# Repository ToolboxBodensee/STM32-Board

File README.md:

# STM32-Board

**Entwicklung nur auf [GitLab](https://gitlab.com/ToolboxBodensee/microcontroller/STM32-Board). Auf GitHub befindet sich lediglich ein Mirror**

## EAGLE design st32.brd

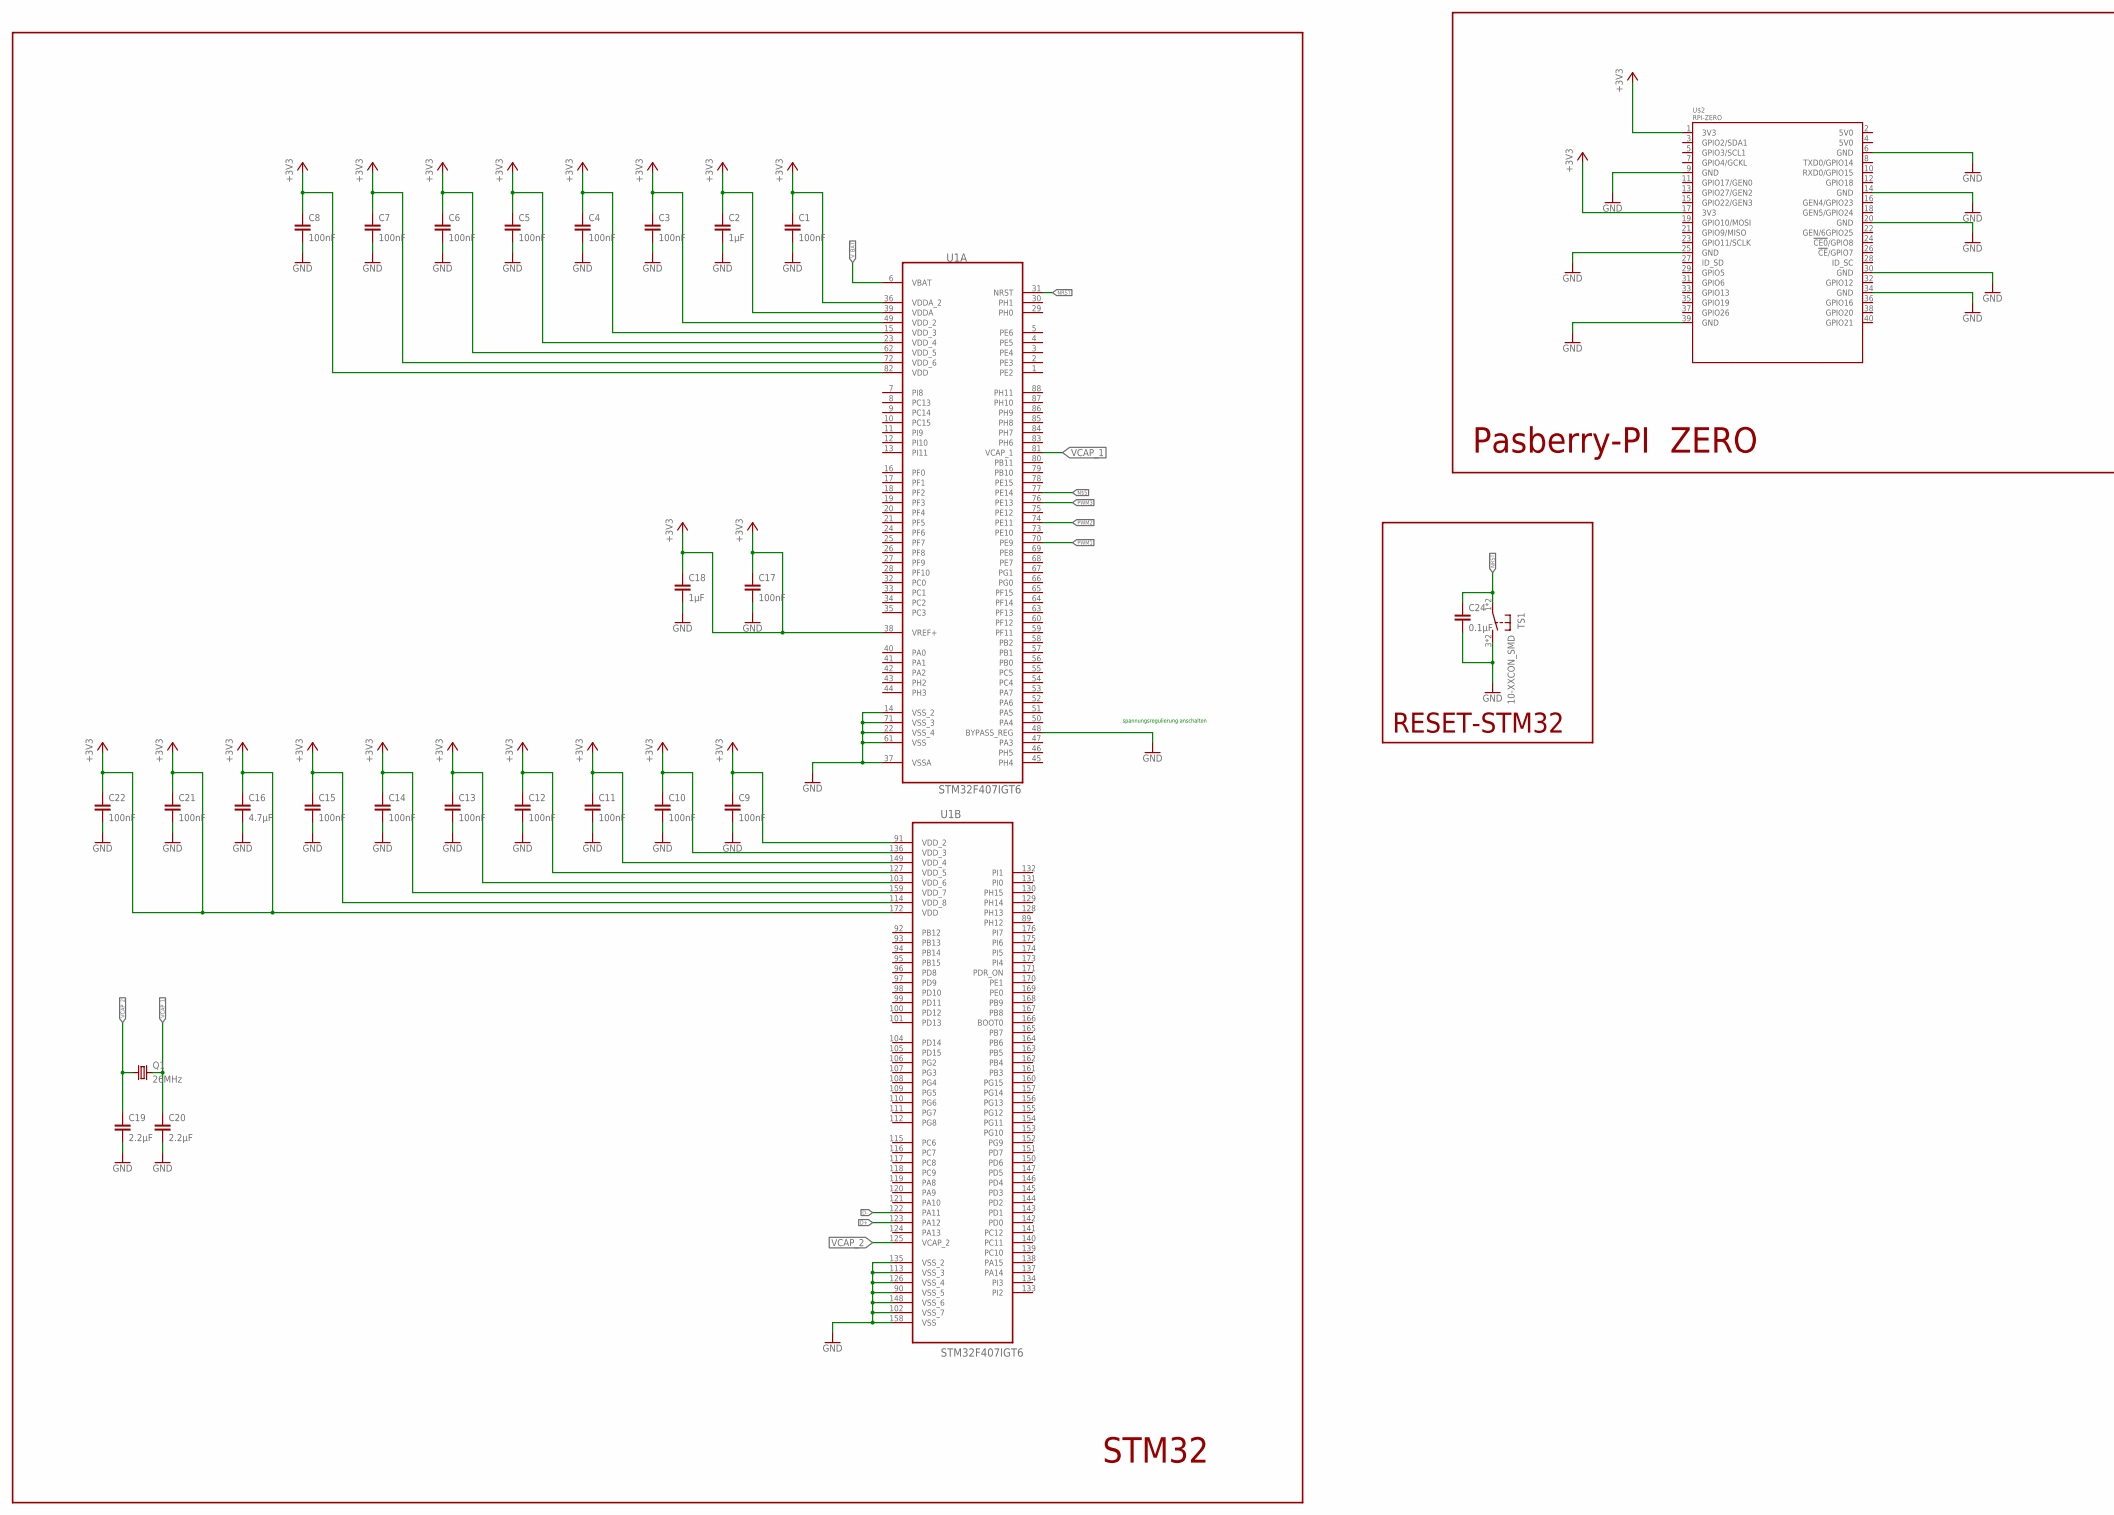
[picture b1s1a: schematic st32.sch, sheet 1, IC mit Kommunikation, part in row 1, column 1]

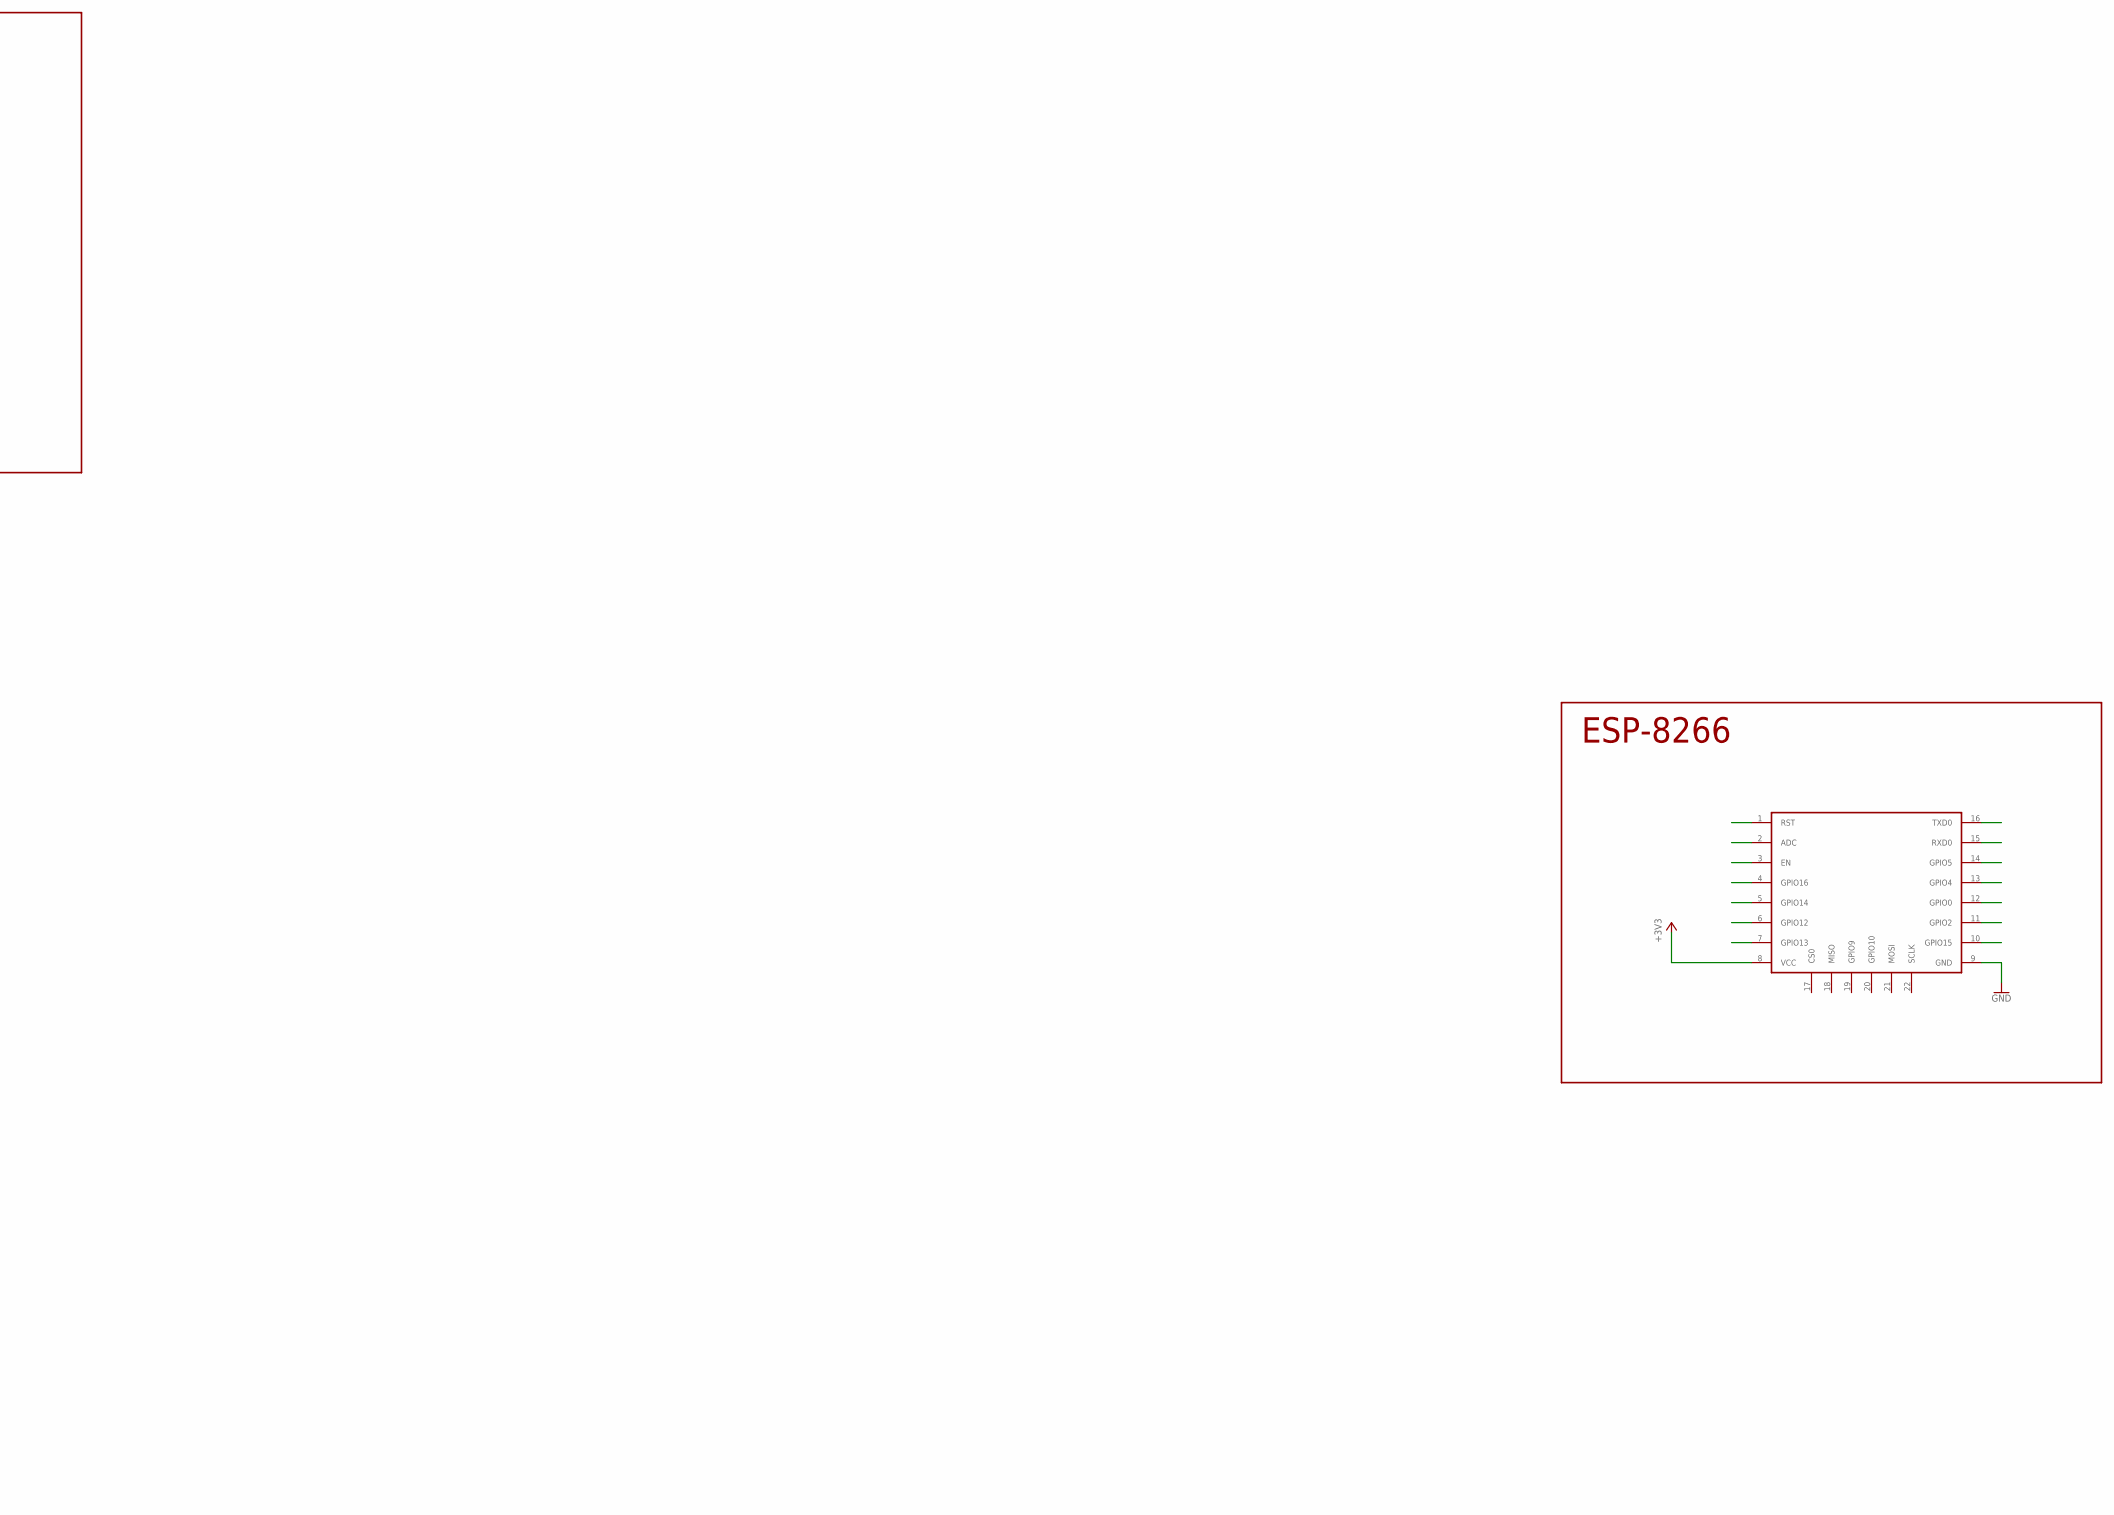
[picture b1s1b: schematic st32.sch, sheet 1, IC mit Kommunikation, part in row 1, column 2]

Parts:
C1, C3, C4, C5, C6, C7, C8, C9, C10, C11, C12, C13, C14, C15, C17, C21, C22: 100nF; C0603
C2, C18: 1µF; C0603
C16: 4.7µF; C0603
C19, C20: 2.2µF; C0603
C24: 0.1µF; C0603
Q1: 26MHz; HC49UP
TS1: 10-XXCON_SMD; SKHMPXE010
U1: STM32F407IGT6; QFP50P2600X2600X160-176N
U$1: ESP8266; ESP8266-SMT
U$2: RPI-ZERO; RASPBERRYPI_BASTELSTUBE_V13_RASPI_BOARD_B+_FULL

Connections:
+3V3: C1.1, C2.1, C3.1, C4.1, C5.1, C6.1, C7.1, C8.1, C9.1, C10.1, C11.1, C12.1, C13.1, C14.1, C15.1, C16.1, C17.1, C18.1, C21.1, C22.1, U1.15 (VDD_3), U1.23 (VDD_4), U1.36 (VDDA_2), U1.38 (VREF+), U1.39 (VDDA), U1.49 (VDD_2), U1.62 (VDD_5), U1.72 (VDD_6), U1.82 (VDD), U1.91 (VDD_2), U1.103 (VDD_6), U1.114 (VDD_8), U1.127 (VDD_5), U1.136 (VDD_3), U1.149 (VDD_4), U1.159 (VDD_7), U1.172 (VDD), U$1.8 (VCC), U$2.1 (3V3), U$2.17 (3V3); also elsewhere on the board
D+: U1.123 (PA12); also elsewhere on the board
D-: U1.122 (PA11); also elsewhere on the board
GND_PWR: C1.2, C2.2, C3.2, C4.2, C5.2, C6.2, C7.2, C8.2, C9.2, C10.2, C11.2, C12.2, C13.2, C14.2, C15.2, C16.2, C17.2, C18.2, C19.2, C20.2, C21.2, C22.2, C24.2, TS1.3 (S), TS1.4 (S), U1.14 (VSS_2), U1.22 (VSS_4), U1.37 (VSSA), U1.48 (BYPASS_REG), U1.61 (VSS), U1.71 (VSS_3), U1.90 (VSS_5), U1.102 (VSS_7), U1.113 (VSS_3), U1.126 (VSS_4), U1.135 (VSS_2), U1.148 (VSS_6), U1.158 (VSS), U$1.9 (GND), U$2.6 (GND), U$2.9 (GND), U$2.14 (GND), U$2.20 (GND), U$2.25 (GND), U$2.30 (GND), U$2.34 (GND), U$2.39 (GND); also elsewhere on the board
NRST: C24.1, TS1.1, TS1.2, U1.31 (NRST)
PWM1: U1.70 (PE9)
PWM2: U1.74 (PE11)
PWM3: U1.76 (PE13)
VCAP_1: C20.1, Q1.2, U1.81 (VCAP_1)
VCAP_2: C19.1, Q1.1, U1.125 (VCAP_2)
V_BAT: U1.6 (VBAT); also elsewhere on the board

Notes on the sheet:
spannungsregulierung anschalten
STM32
Pasberry-PI ZERO
ESP-8266
RESET-STM32

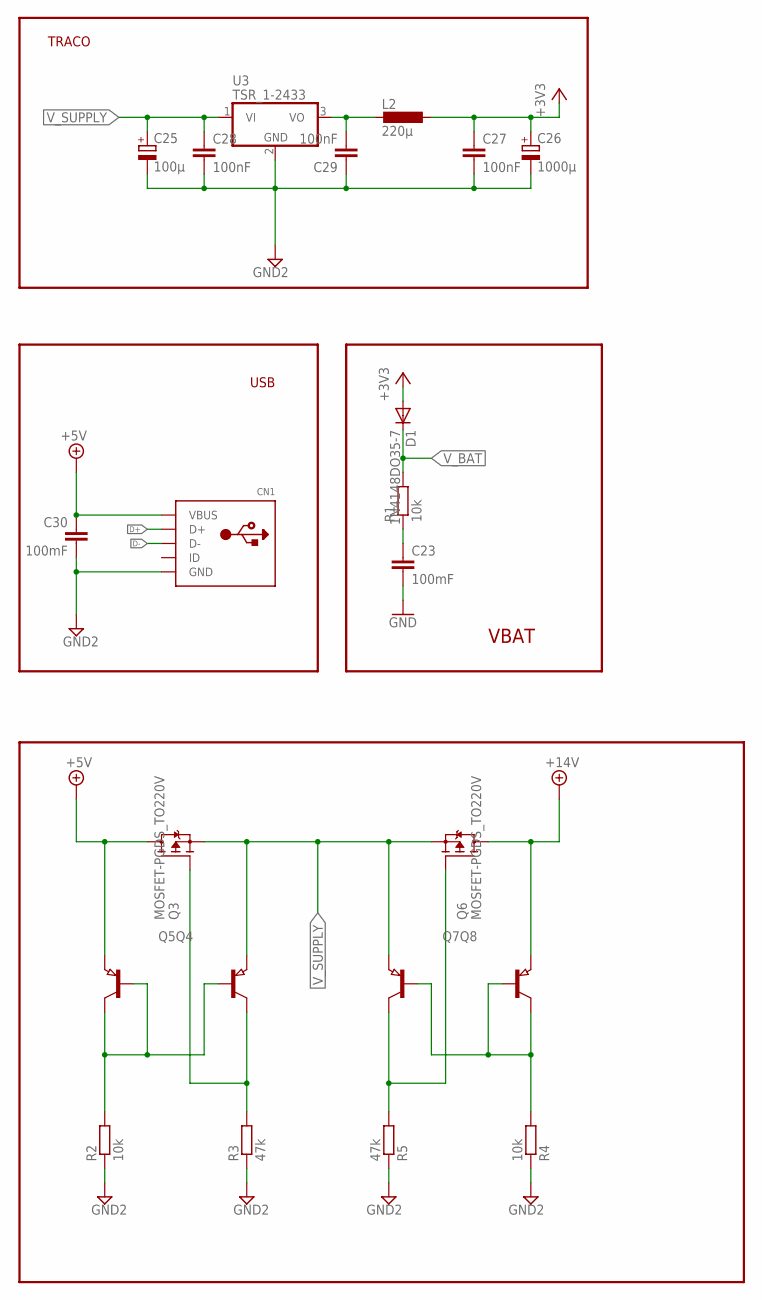
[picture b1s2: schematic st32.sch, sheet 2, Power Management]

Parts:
C23, C30: 100mF; C0603
C25: 100µ; E2,5-6
C26: 1000µ; E5-13
C27, C28, C29: 100nF; C1206
CN1: USBMINIB; USB-MINIB
D1: 1N4148DO35-7; DO35-7
L2: 220µ; TJ3-U1
Q3, Q6: MOSFET-PGDS_TO220V; TO220V
Q4, Q5, Q7, Q8: PNP-TRANSISTOR_SOT23; SOT23
R1: 10k; R0603
R2, R4: 10k; M1206
R3, R5: 47k; M1206
U3: TSR_1-2433; TSR-1

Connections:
+3V3: C26.+, C27.1, D1.A, L2.1; also elsewhere on the board
+5V: C30.1, CN1.VBUS, Q3.2 (D), Q5.2 (E)
+14V: Q6.2 (D), Q8.2 (E); also elsewhere on the board
D+: CN1.D+; also elsewhere on the board
D-: CN1.D-; also elsewhere on the board
GND2: C25.-, C26.-, C27.2, C28.2, C29.1, C30.2, CN1.GND, R2.1, R3.1, R4.1, R5.1, U3.2 (GND)
GND_PWR: C23.2; also elsewhere on the board
unnamed: C23.1, R1.1
unnamed: Q4.1 (B), Q5.1 (B), Q5.3 (C), R2.2
unnamed: Q3.1 (G), Q4.3 (C), R3.2
unnamed: Q7.1 (B), Q8.1 (B), Q8.3 (C), R4.2
unnamed: Q6.1 (G), Q7.3 (C), R5.2
unnamed: C29.2, L2.2, U3.3 (VO)
V_BAT: D1.C, R1.2; also elsewhere on the board
V_SUPPLY: C25.+, C28.1, Q3.3 (S), Q4.2 (E), Q6.3 (S), Q7.2 (E), U3.1 (VI)

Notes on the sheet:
USB
TRACO
VBAT

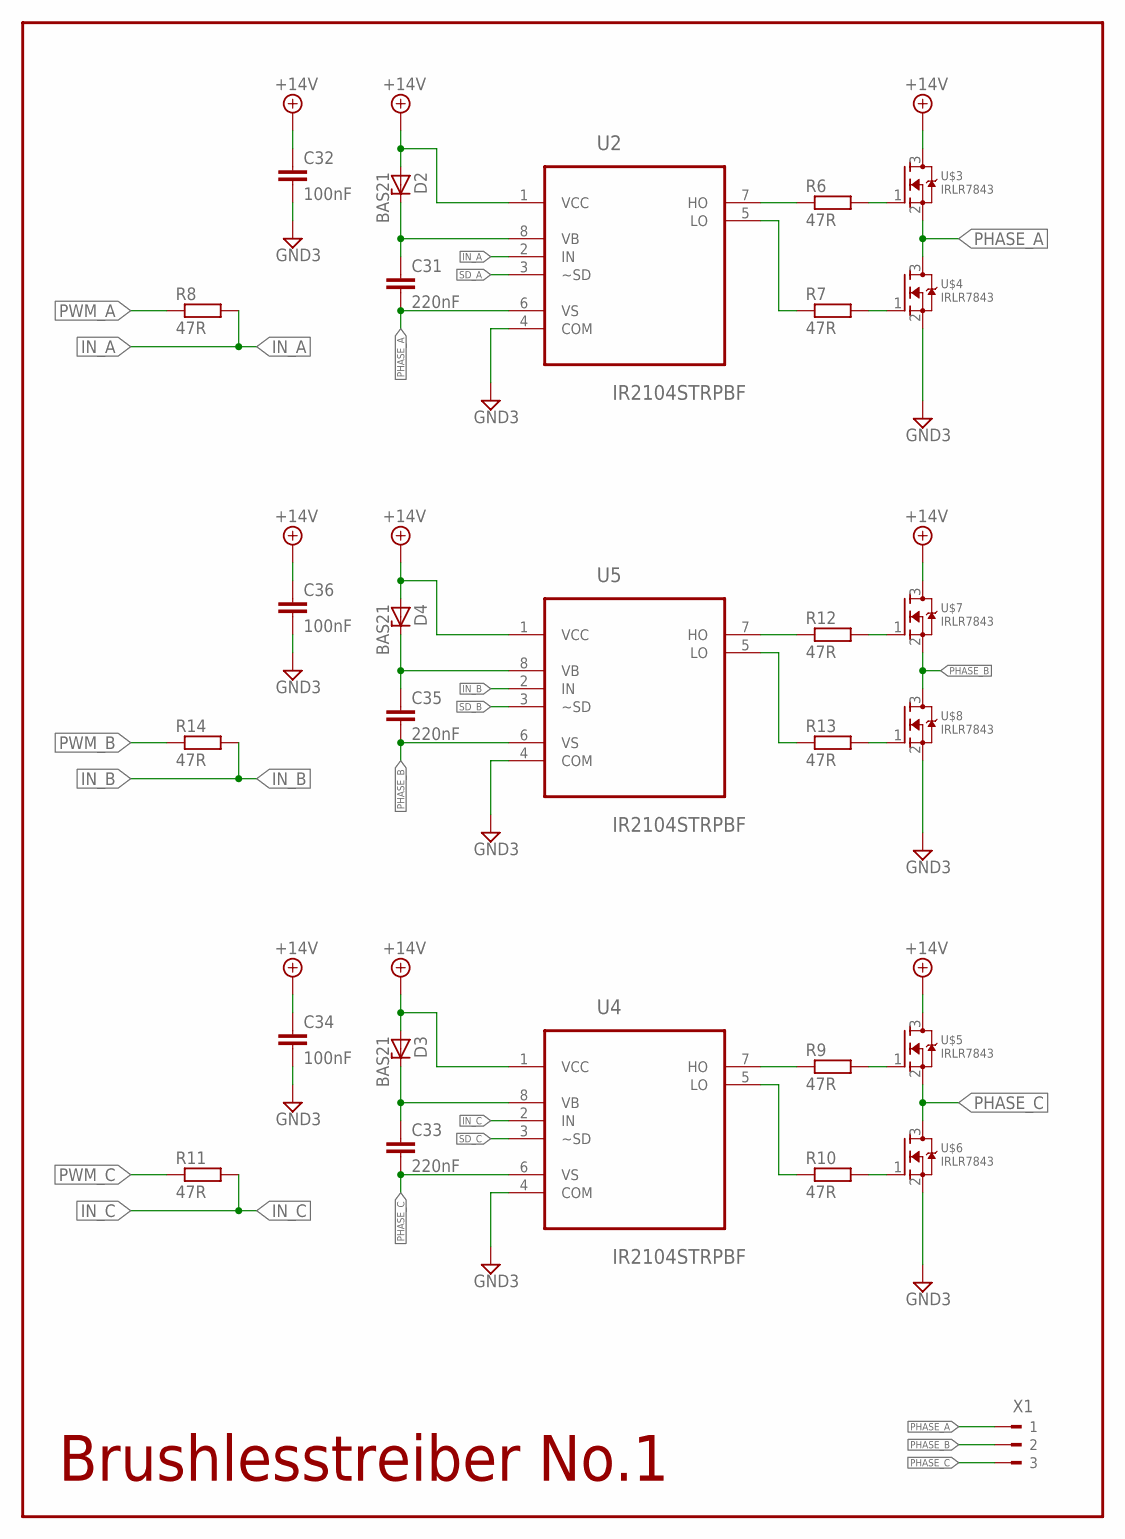
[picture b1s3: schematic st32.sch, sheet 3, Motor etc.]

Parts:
C31, C33, C35: 220nF; C0805
C32, C34, C36: 100nF; C0805
D2, D3, D4: BAS21; SOT23
R6, R7, R8, R9, R10, R11, R12, R13, R14: 47R; M0805
U2, U4, U5: IR2104STRPBF; SOIC127P600X175-8N
U$3, U$4, U$5, U$6, U$7, U$8: IRLR7843; D-PACK
X1: 90-3

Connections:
+14V: C32.1, C34.1, C36.1, D2.1 (A), D3.1 (A), D4.1 (A), U2.1 (VCC), U4.1 (VCC), U5.1 (VCC), U$3.3 (D), U$5.3 (D), U$7.3 (D); also elsewhere on the board
GND3: C32.2, C34.2, C36.2, U2.4 (COM), U4.4 (COM), U5.4 (COM), U$4.2 (S), U$6.2 (S), U$8.2 (S)
IN_A: R8.2, U2.2 (IN)
IN_B: R14.2, U5.2 (IN)
IN_C: R11.2, U4.2 (IN)
unnamed: R6.2, U$3.1 (G)
unnamed: C31.1, D2.3 (C), U2.8 (VB)
unnamed: R7.1, U2.5 (LO)
unnamed: R6.1, U2.7 (HO)
unnamed: R7.2, U$4.1 (G)
unnamed: C33.1, D3.3 (C), U4.8 (VB)
unnamed: R10.1, U4.5 (LO)
unnamed: R9.1, U4.7 (HO)
unnamed: R10.2, U$6.1 (G)
unnamed: R9.2, U$5.1 (G)
unnamed: C35.1, D4.3 (C), U5.8 (VB)
unnamed: R13.1, U5.5 (LO)
unnamed: R12.1, U5.7 (HO)
unnamed: R13.2, U$8.1 (G)
unnamed: R12.2, U$7.1 (G)
PHASE_A: C31.2, U2.6 (VS), U$3.2 (S), U$4.3 (D), X1.1
PHASE_B: C35.2, U5.6 (VS), U$7.2 (S), U$8.3 (D), X1.2
PHASE_C: C33.2, U4.6 (VS), U$5.2 (S), U$6.3 (D), X1.3
PWM_A: R8.1
PWM_B: R14.1
PWM_C: R11.1
SD_A: U2.3 (~SD)
SD_B: U5.3 (~SD)
SD_C: U4.3 (~SD)

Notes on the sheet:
Brushlesstreiber No.1

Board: 2 copper layers, 78 parts (0 on the bottom side), 40 nets, no tracks yet.

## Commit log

2015-12-17 .gitignore und einige schaltplan anfänge
2015-12-21 power
2015-12-31 Brushlesstreiber 1. Ansatz(brauchen wir das?;)
2019-11-28 add gitlab warning
